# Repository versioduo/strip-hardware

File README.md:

# strip-hardware
🚦 LED strip hardware

## Board

## Video
[YouTube](https://www.youtube.com/watch?v=P1gKQrn-1O4)

## Schematic

[PDF](strip.pdf)

## Bill Of Materials

[Interactive BOM](https://htmlpreview.github.io/?https://github.com/versioduo/strip-hardware/main/strip-bom.html)

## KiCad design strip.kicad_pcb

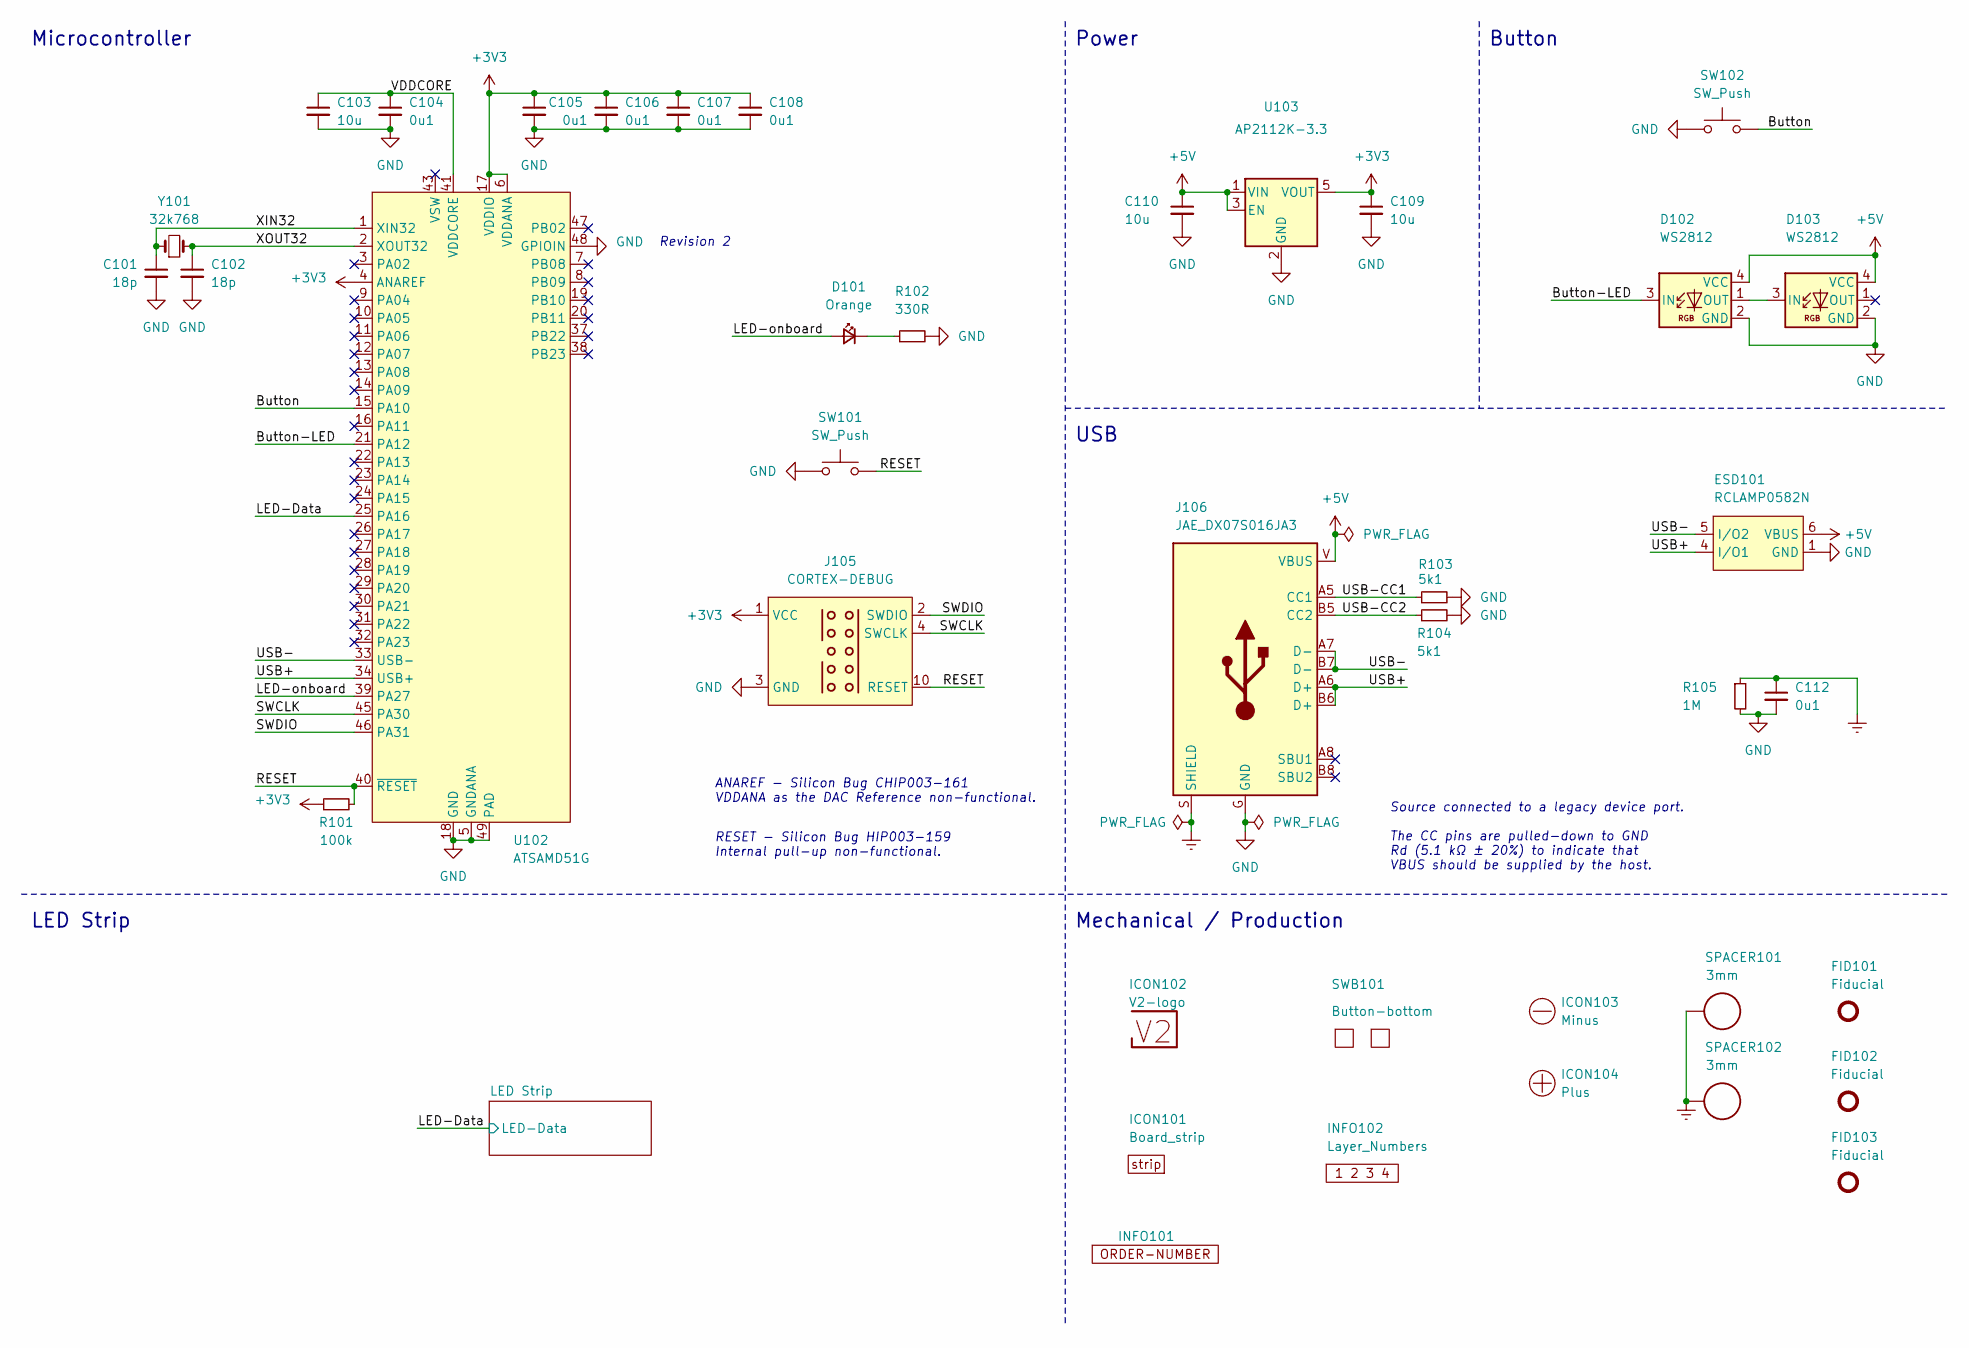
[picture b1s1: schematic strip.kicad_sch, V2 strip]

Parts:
C101, C102: 18p; C_0603_1608Metric
C103, C109, C110: 10u; C_0603_1608Metric
C104, C105, C106, C107, C108, C112: 0u1; C_0603_1608Metric
D101: Orange; LED_0603_1608Metric
D102, D103: WS2812; WS2812-2020
ESD101: RCLAMP0582N; SLP1210N6
FID101, FID102, FID103: Fiducial; Fiducial_0.5mm_Mask1mm_Paste
ICON101: Board_strip; Board_strip_Small
ICON102: V2-logo; Logo_Small
ICON103: Minus; Minus_Small
ICON104: Plus; Plus_Small
INFO101: ORDER-NUMBER; Order_Number
INFO102: Layer_Numbers
J105: CORTEX-DEBUG; Cortex_Debug_Pad
J106: JAE_DX07S016JA3
R101: 100k; R_0603_1608Metric
R102: 330R; R_0603_1608Metric
R103, R104: 5k1; R_0603_1608Metric
R105: 1M; R_0603_1608Metric
SPACER101, SPACER102: 3mm; 9774030243
SW101, SW102: SW_Push; SKSG
SWB101: Button-bottom; PCB_Button-bottom
U102: ATSAMD51G; QFN-48-1EP_7x7mm_P0.5mm_EP5.45x5.45mm_ThermalVias
U103: AP2112K-3.3; SOT-23-5
Y101: 32k768; Crystal_SMD_3215-2Pin_3.2x1.5mm

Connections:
+3V3: C105.1, C106.1, C107.1, C108.1, C109.1, J105.1 (VCC), R101.1, U102.4 (ANAREF), U102.6 (VDDANA), U102.17 (VDDIO), U102.36 (VDDIO), U102.44 (VDDIO), U103.5 (VOUT)
+5V: C110.1, D102.4 (VCC), D103.4 (VCC), ESD101.6 (VBUS), J106.V (VBUS), U103.1 (VIN), U103.3 (EN); also elsewhere on the board
/Button: SW102.2, U102.15 (PA10)
/Button-LED: D102.3 (IN), U102.21 (PA12)
/LED-Data: U102.25 (PA16); also elsewhere on the board
/LED-onboard: D101.2 (A), U102.39 (PA27)
/RESET: J105.10 (RESET), R101.2, SW101.2, U102.40 (~RESET)
/SWCLK: J105.4 (SWCLK), U102.45 (PA30)
/SWDIO: J105.2 (SWDIO), U102.46 (PA31)
/USB+: ESD101.4 (I/O1), J106.A6 (D+), J106.B6 (D+), U102.34 (USB+)
/USB-: ESD101.5 (I/O2), J106.A7 (D-), J106.B7 (D-), U102.33 (USB-)
/USB-CC1: J106.A5 (CC1), R103.1
/USB-CC2: J106.B5 (CC2), R104.1
/VDDCORE: C103.1, C104.1, U102.41 (VDDCORE)
/XIN32: C101.1, U102.1 (XIN32), Y101.1
/XOUT32: C102.1, U102.2 (XOUT32), Y101.2
Earth: C112.1, J106.S (SHIELD), R105.1, SPACER101.1, SPACER102.1
GND: C101.2, C102.2, C103.2, C104.2, C105.2, C106.2, C107.2, C108.2, C109.2, C110.2, C112.2, D102.2 (GND), D103.2 (GND), ESD101.1 (GND), J105.3 (GND), J105.5 (GND), J106.G (GND), R102.2, R103.2, R104.2, R105.2, SW101.1, SW102.1, U102.5 (GNDANA), U102.18 (GND), U102.35 (GND), U102.42 (GND), U102.48 (GPIOIN), U102.49 (PAD), U103.2 (GND); also elsewhere on the board
unnamed: D101.1 (K), R102.1
unnamed: D102.1 (OUT), D103.3 (IN)

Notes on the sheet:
ANAREF - ﻿Silicon Bug CHIP003-161 VDDANA as the DAC Reference non-functional.
RESET - ﻿Silicon Bug HIP003-159 Internal pull-up non-functional.
﻿Source connected to a legacy device port. The CC pins are pulled-down to GND Rd (5.1 kΩ ± 20%) to indicate that VBUS should be supplied by the host.
Button
Revision 2
Power
Mechanical / Production
Microcontroller
USB
LED Strip

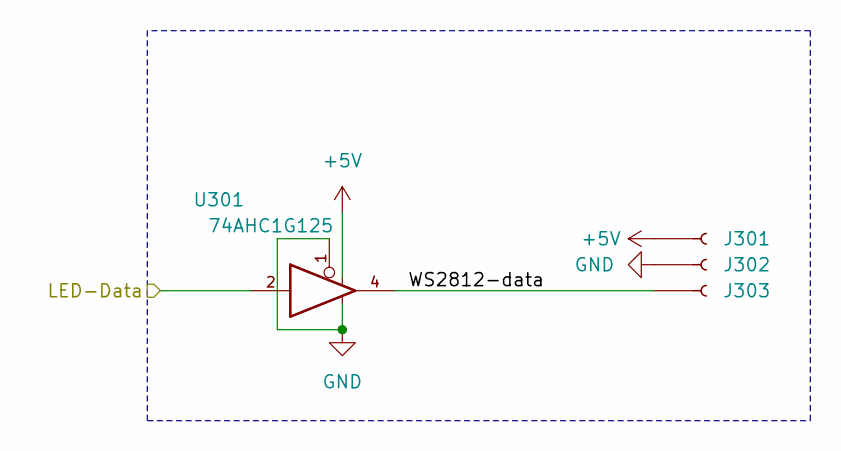
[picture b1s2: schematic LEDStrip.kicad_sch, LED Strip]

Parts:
J301, J302, J303: WAGO-2065; 2065-100
U301: 74AHC1G125; SOT-23-5

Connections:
+5V: J301.1, U301.5; also elsewhere on the board
/LED Strip/WS2812-data: J303.1, U301.4
/LED-Data: U301.2; also elsewhere on the board
GND: J302.1, U301.1, U301.3; also elsewhere on the board

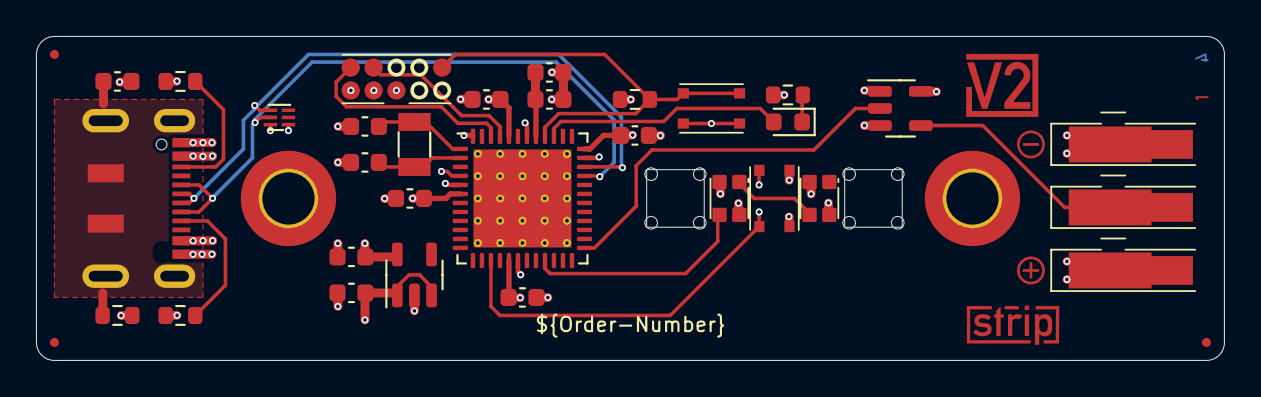
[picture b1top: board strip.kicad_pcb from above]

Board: 4 copper layers, 66.0 x 18.0 mm, 43 parts (0 on the bottom side), 21 nets.

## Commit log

2023-01-06 Import
2023-09-12 Refresh
2024-03-28 Update to Kicad 8
2024-03-31 Udpate vias
